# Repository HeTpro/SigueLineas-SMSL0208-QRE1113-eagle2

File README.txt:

HeTPro - Herramientas Tecnologicas Profesionales
Guadalajara, Jalisco. 

Diseño creado bajo la licencia CC Creative Commons

Attribution-ShareAlike 4.0 International (CC BY-SA 4.0) 
http://creativecommons.org/licenses/by-sa/4.0/

www.hetpro.com.mx
contacto@hetpro.com.mx

El diseño creado bajo esta licencia es libre de:

Compartir - Compartir y distribuir el material en culquier medio o formato.
Modificar - Adaptar, transformar y reconstruir el material.

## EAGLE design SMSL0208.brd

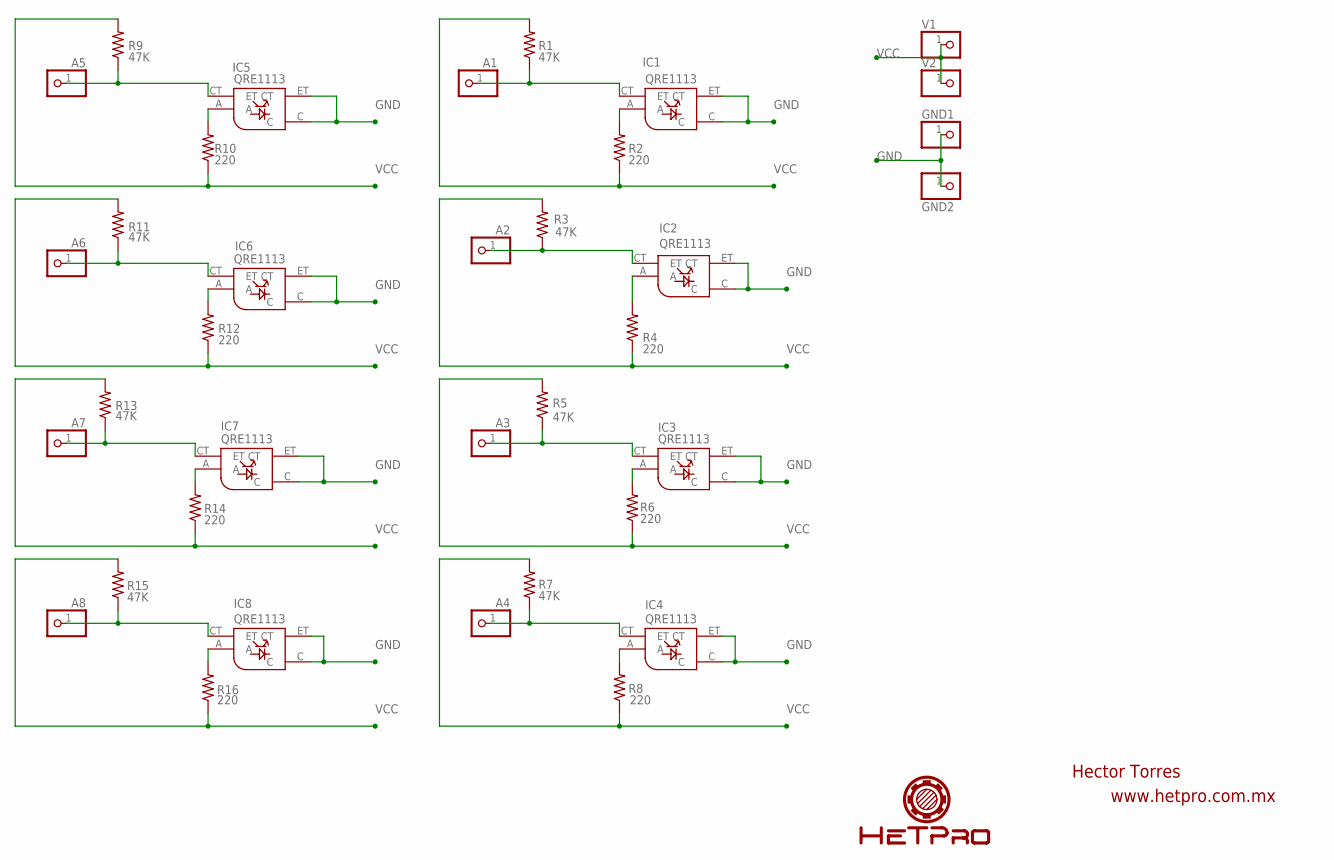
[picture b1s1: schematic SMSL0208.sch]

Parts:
A1, A2, A3, A4, A5, A6, A7, A8: PINHD-1X1; 1X01
GND1, GND2: PINHD-1X1; 1X01
IC1, IC2, IC3, IC4, IC5, IC6, IC7, IC8: QRE1113
R1, R3, R5, R7, R9, R11, R13, R15: 47K; R0603
R2, R4, R6, R8, R10, R12, R14, R16: 220; R0603
V1, V2: PINHD-1X1; 1X01

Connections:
GND: GND1.1, GND2.1, IC1.C, IC1.ET (CT), IC2.C, IC2.ET (CT), IC3.C, IC3.ET (CT), IC4.C, IC4.ET (CT), IC5.C, IC5.ET (CT), IC6.C, IC6.ET (CT), IC7.C, IC7.ET (CT), IC8.C, IC8.ET (CT)
unnamed: IC1.A, R2.2
unnamed: A1.1, IC1.CT (ET), R1.1
unnamed: A2.1, IC2.CT (ET), R3.1
unnamed: A5.1, IC5.CT (ET), R9.1
unnamed: IC2.A, R4.2
unnamed: IC5.A, R10.2
unnamed: A3.1, IC3.CT (ET), R5.1
unnamed: IC3.A, R6.2
unnamed: A6.1, IC6.CT (ET), R11.1
unnamed: A4.1, IC4.CT (ET), R7.1
unnamed: IC4.A, R8.2
unnamed: IC6.A, R12.2
unnamed: A8.1, IC8.CT (ET), R15.1
unnamed: IC8.A, R16.2
unnamed: A7.1, IC7.CT (ET), R13.1
unnamed: IC7.A, R14.2
VCC: R1.2, R2.1, R3.2, R4.1, R5.2, R6.1, R7.2, R8.1, R9.2, R10.1, R11.2, R12.1, R13.2, R14.1, R15.2, R16.1, V1.1, V2.1

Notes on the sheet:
www.hetpro.com.mx
Hector Torres

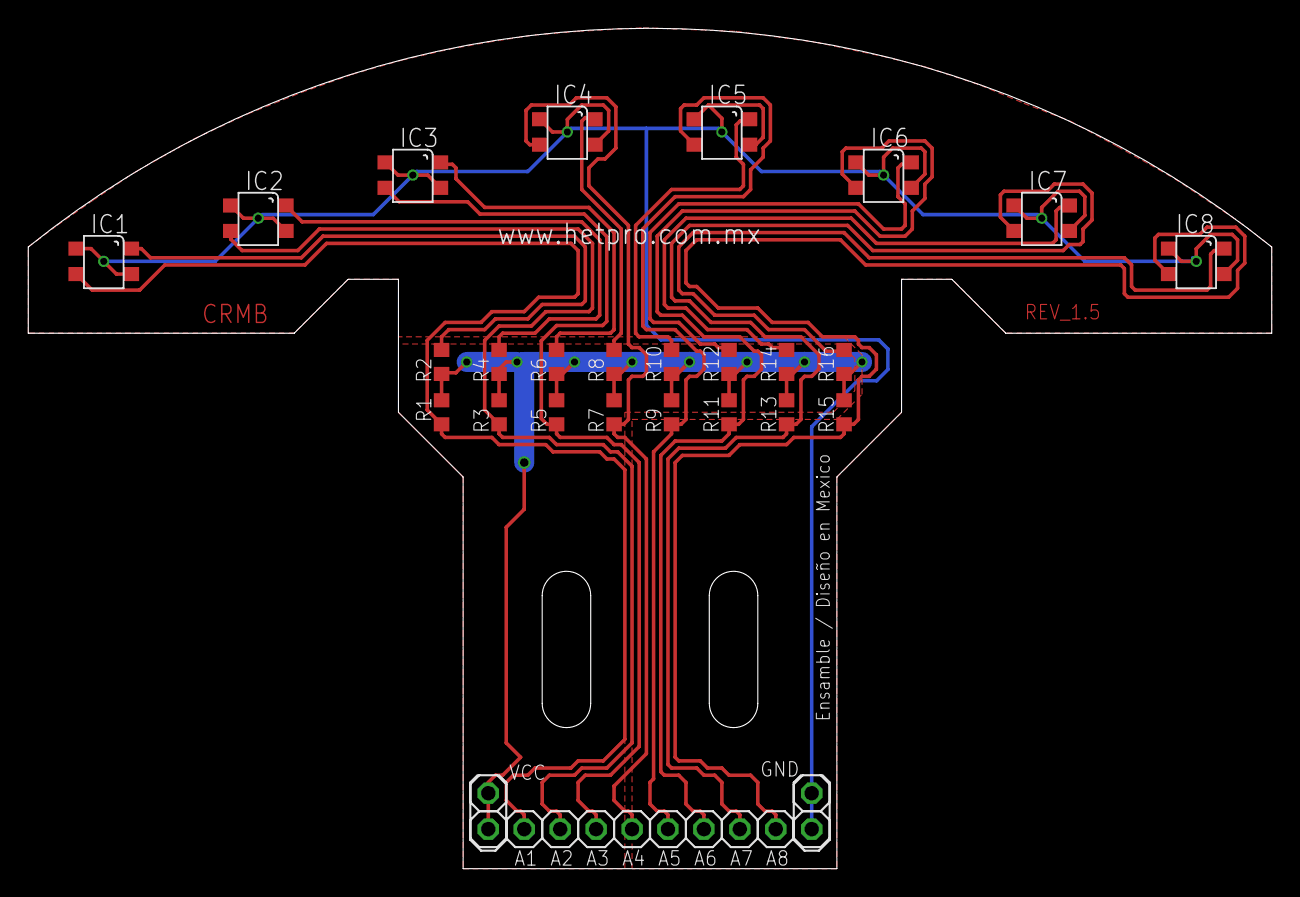
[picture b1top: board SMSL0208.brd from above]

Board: 2 copper layers, 87.9 x 59.4 mm, 36 parts (0 on the bottom side), 18 nets.

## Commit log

2014-10-04 :tada: Added .gitattributes & .gitignore files
2014-10-04 Add files
    files added.
